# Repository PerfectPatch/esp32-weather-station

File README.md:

# esp32-weather-station

ESP32-based weather station with a BME280 sensor and a 16x2 LCD display.
It measures temperature, humidity and pressure and shows them on the LCD. Runs on 3×AA batteries.

## Features

- Temperature, humidity and pressure from a BME280 (I²C)
- 16x2 LCD driven in 4-bit parallel mode, contrast set by a potentiometer
- Runs on 3×AA batteries with a power switch
- Custom carrier PCB designed in KiCad
- 3D-printed enclosure designed in FreeCAD

## Hardware

| Part | Notes |
|---|---|
| ESP32 DevKit V1 (30-pin, ESP32-WROOM-32) | plugs into two 1×15 headers |
| BME280 module | 4-pin I²C (VIN, GND, SCL, SDA), right-angle header on the board edge |
| LCD 1602 (HD44780-compatible) | 4-bit mode, R/W tied to GND |
| 10 kΩ potentiometer | LCD contrast |
| Switch | in series with battery + |
| 3×AA battery holder | ~4.5 V into VIN |

## Wiring

| From | To (ESP32) |
|---|---|
| BME280 SDA | GPIO21 |
| BME280 SCL | GPIO22 |
| BME280 VIN | 3V3 |
| LCD RS | GPIO19 |
| LCD E | GPIO23 |
| LCD D4 | GPIO18 |
| LCD D5 | GPIO17 |
| LCD D6 | GPIO16 |
| LCD D7 | GPIO4 |
| LCD V0 | potentiometer wiper |
| LCD VDD, A | battery + (after switch) |
| LCD VSS, R/W, K | GND |
| Battery + (after switch) | VIN |

All grounds are common.

## PCB

A carrier board designed in KiCad that replaces the jumper wires. The ESP32 DevKit, BME280 module and LCD plug into headers on the board, the battery holder sits on the back under the display.

| Front | Back |
|---|---|
|  |  |

**Design notes**

- The BME280 is on a right-angle header at the board edge, away from the ESP32 and the display, so it measures room air rather than heat from the electronics.
- v3 drops Wi-Fi. On this board the ESP32 antenna sits over the battery pack and ground pour, so the station is display-only. Without Wi-Fi the ESP32 also draws much less current, which helps battery life.

**Status**

- [x] Schematic
- [x] Footprints and layout
- [ ] Order and assemble
- [ ] Fit the enclosure to the board

Files: [`hardware/pcb`](hardware/pcb)

## Enclosure

The enclosure is designed in FreeCAD as a two-part case joined with snap-fits, so it can be printed and assembled without screws.

- **v1:** printed in PLA, screw-mounted. It needed several screw sizes, and I forgot the power switch and an anti-rotation tab for the potentiometer.
- **v2:** screwless snap-fit case with a power switch, still hand-wired.
- **v3:** custom carrier PCB (this version). The case will be adapted to the board.

Files: [`hardware/enclosure`](hardware/enclosure)

## Building the firmware

1. Install the ESP32 board package in the Arduino IDE.
2. Install the libraries: <!-- list the libraries you actually use, e.g. Adafruit BME280, LiquidCrystal -->
3. Select **ESP32 Dev Module** (or **DOIT ESP32 DEVKIT V1**) and upload.

## Repository structure

```
firmware/            Arduino sketch
hardware/enclosure/  FreeCAD files, STL/3MF for printing
hardware/pcb/        KiCad project and schematic PDF
images/              Photos, schematic and PCB renders
```

## Next steps

- Order and assemble the PCB
- Add deep sleep between measurements to extend battery life
- v4: move the ESP32 antenna past the board edge to bring back Wi-Fi

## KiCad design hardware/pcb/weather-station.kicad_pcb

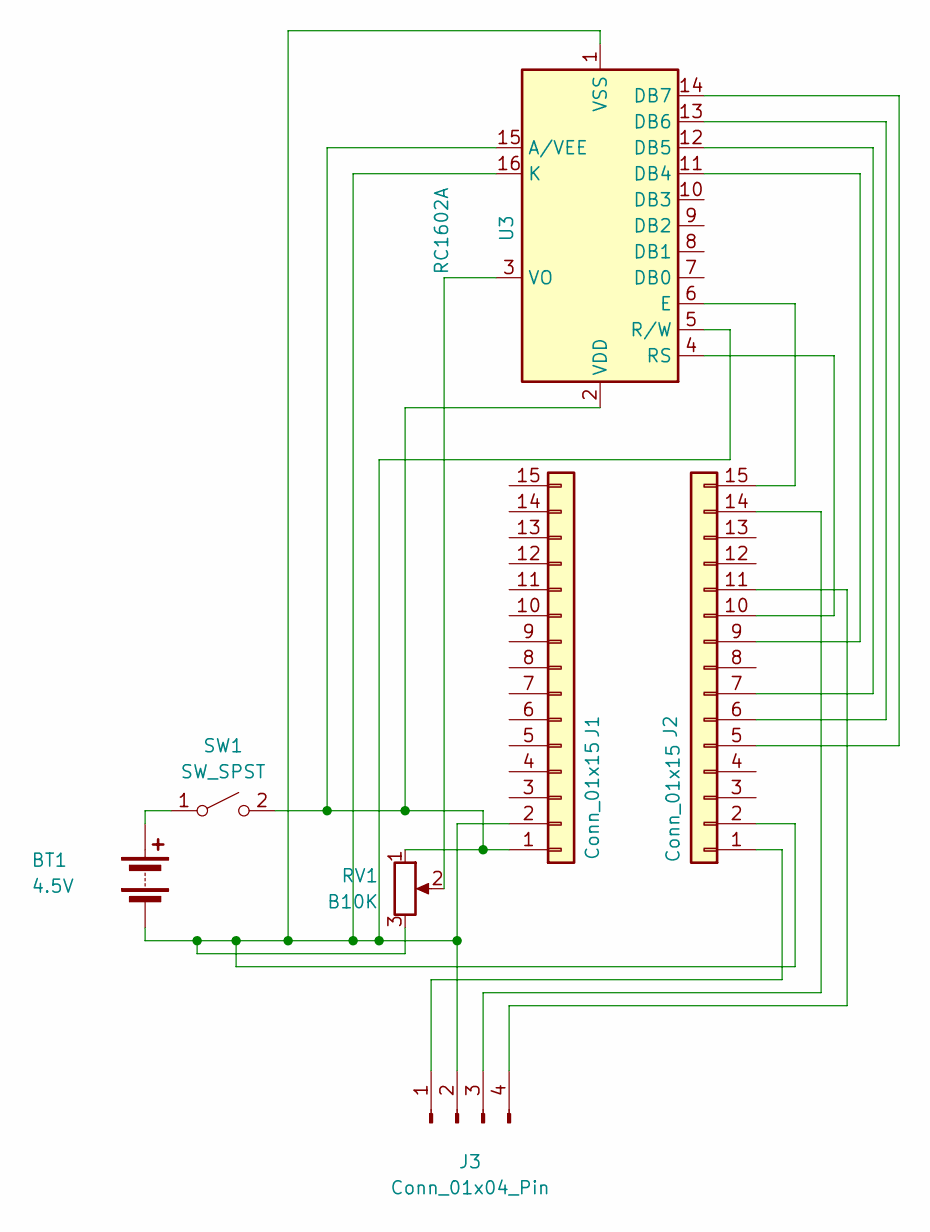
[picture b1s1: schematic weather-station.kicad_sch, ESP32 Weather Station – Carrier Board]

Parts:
BT1: 4.5V; BatteryHolder_Keystone_2479_3xAAA
J1, J2: Conn_01x15; PinHeader_1x15_P2.54mm_Vertical
J3: Conn_01x04_Pin; PinHeader_1x04_P2.54mm_Vertical
RV1: B10K; Potentiometer_Custom_3Pin
SW1: SW_SPST; PinHeader_1x02_P2.54mm_Vertical
U3: RC1602A

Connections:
unnamed: BT1.1 (+), SW1.1 (A)
unnamed: BT1.2 (-), J1.2, J2.2, J3.2, RV1.3, U3.1 (VSS), U3.5 (R/W), U3.16 (K)
unnamed: J1.1, RV1.1, SW1.2 (B), U3.2 (VDD), U3.15 (A/VEE)
unnamed: J2.1, J3.1
unnamed: J2.5, U3.14 (DB7)
unnamed: J2.6, U3.13 (DB6)
unnamed: J2.7, U3.12 (DB5)
unnamed: J2.9, U3.11 (DB4)
unnamed: J2.10, U3.4 (RS)
unnamed: J2.11, J3.4
unnamed: J2.14, J3.3
unnamed: J2.15, U3.6 (E)
unnamed: RV1.2, U3.3 (VO)

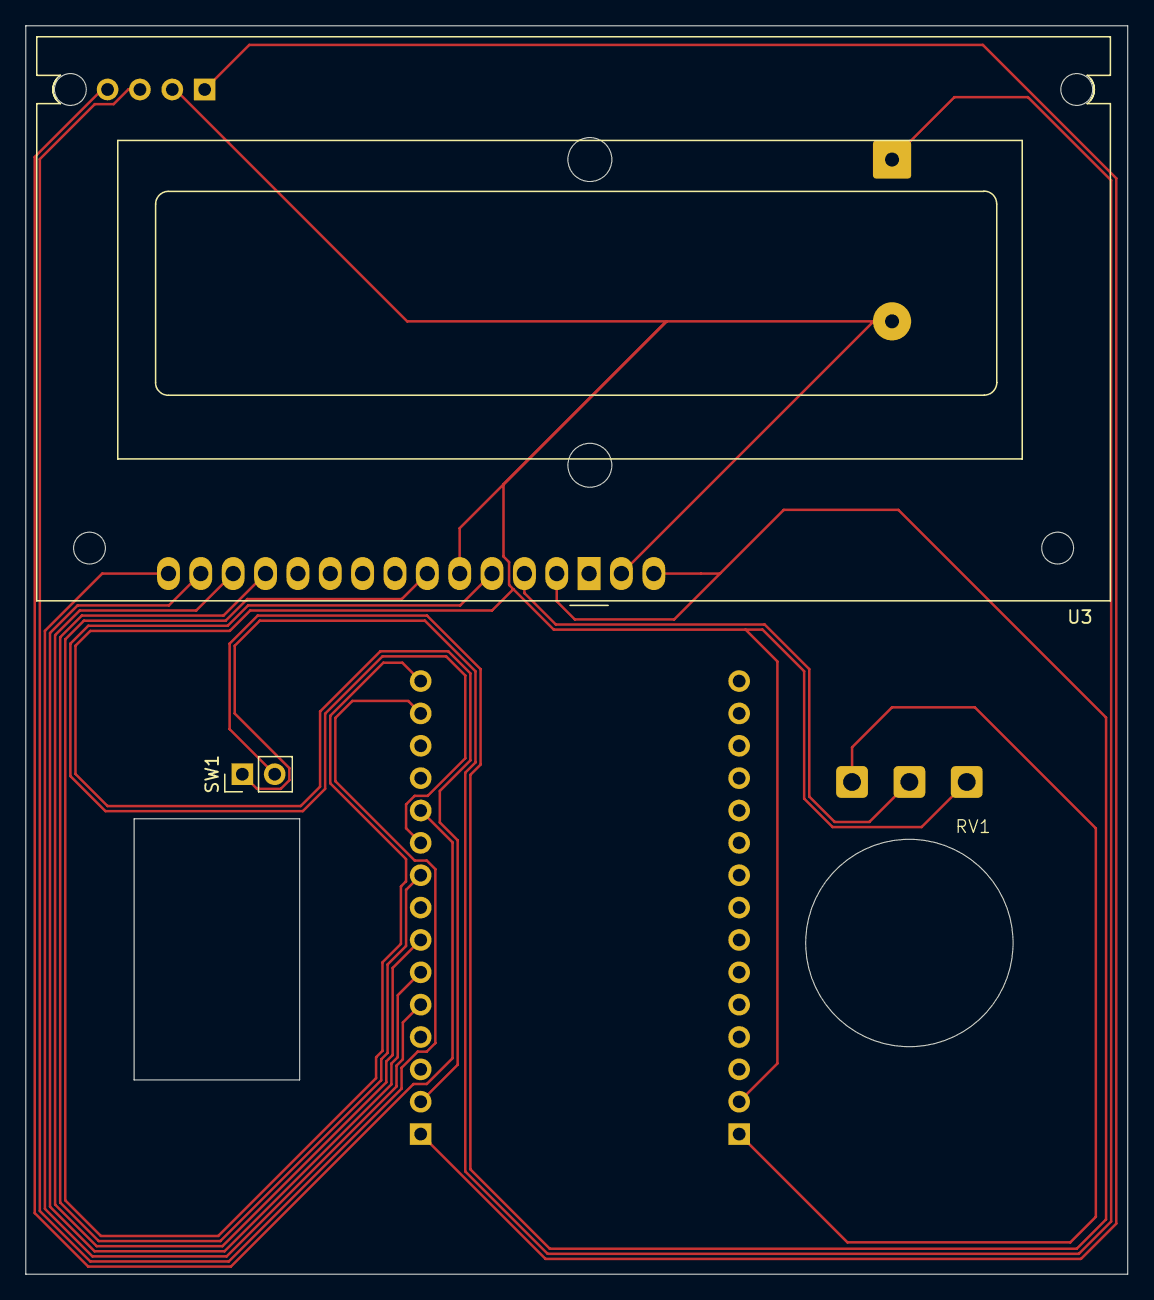
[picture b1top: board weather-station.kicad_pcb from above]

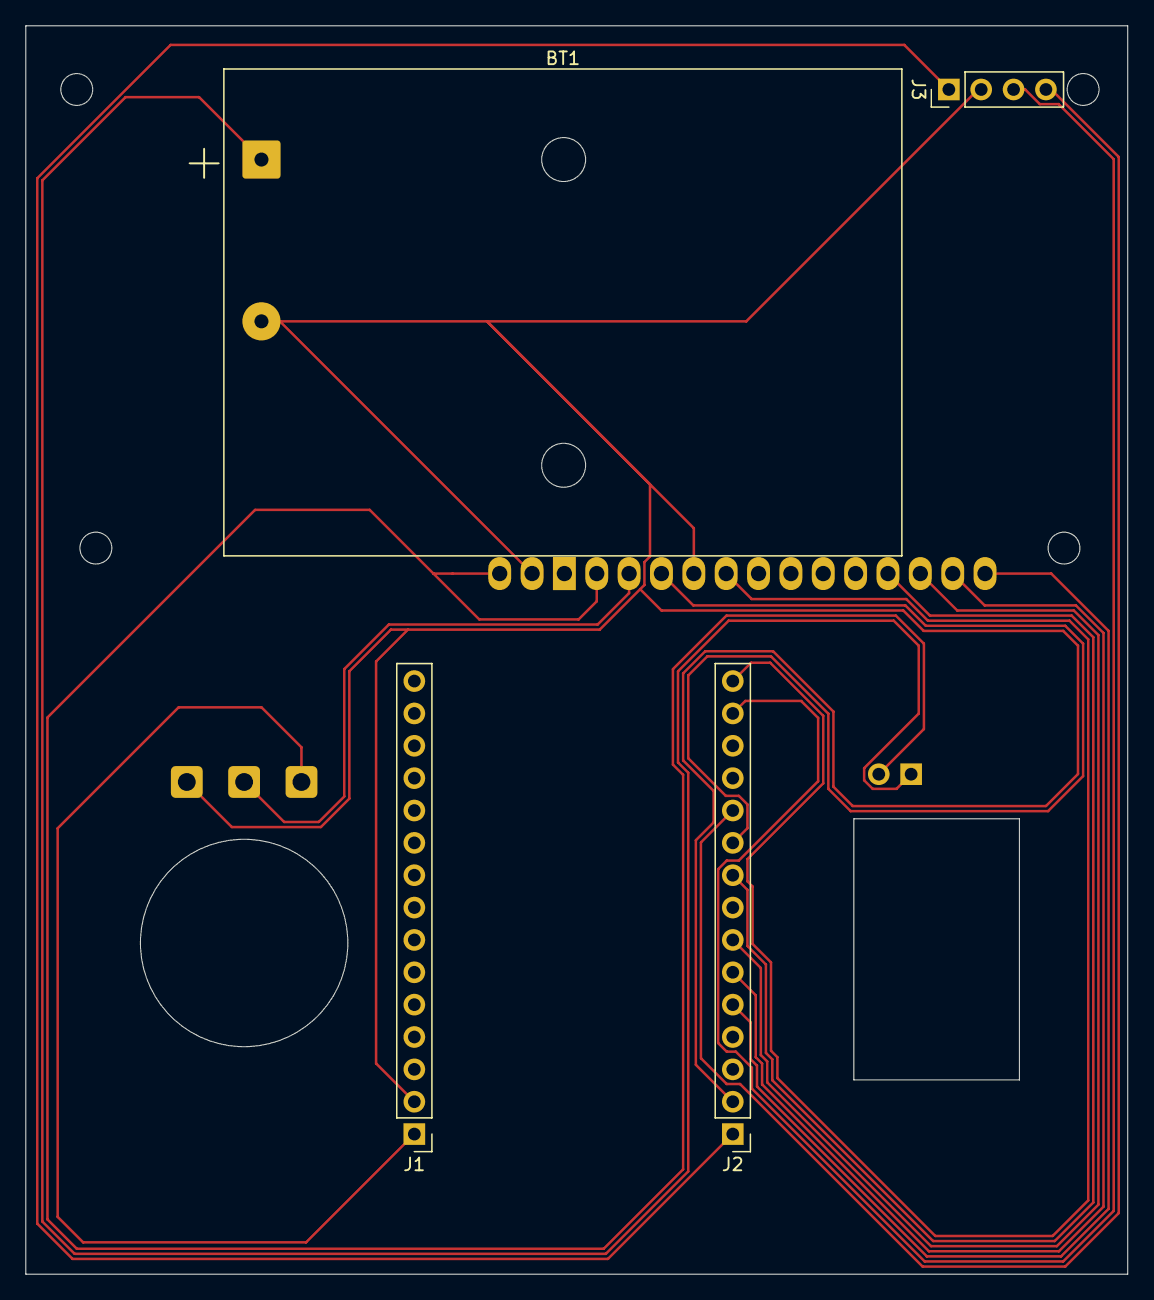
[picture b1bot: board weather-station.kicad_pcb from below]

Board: 2 copper layers, 86.5 x 98.0 mm, 7 parts (4 on the bottom side), 13 nets.
